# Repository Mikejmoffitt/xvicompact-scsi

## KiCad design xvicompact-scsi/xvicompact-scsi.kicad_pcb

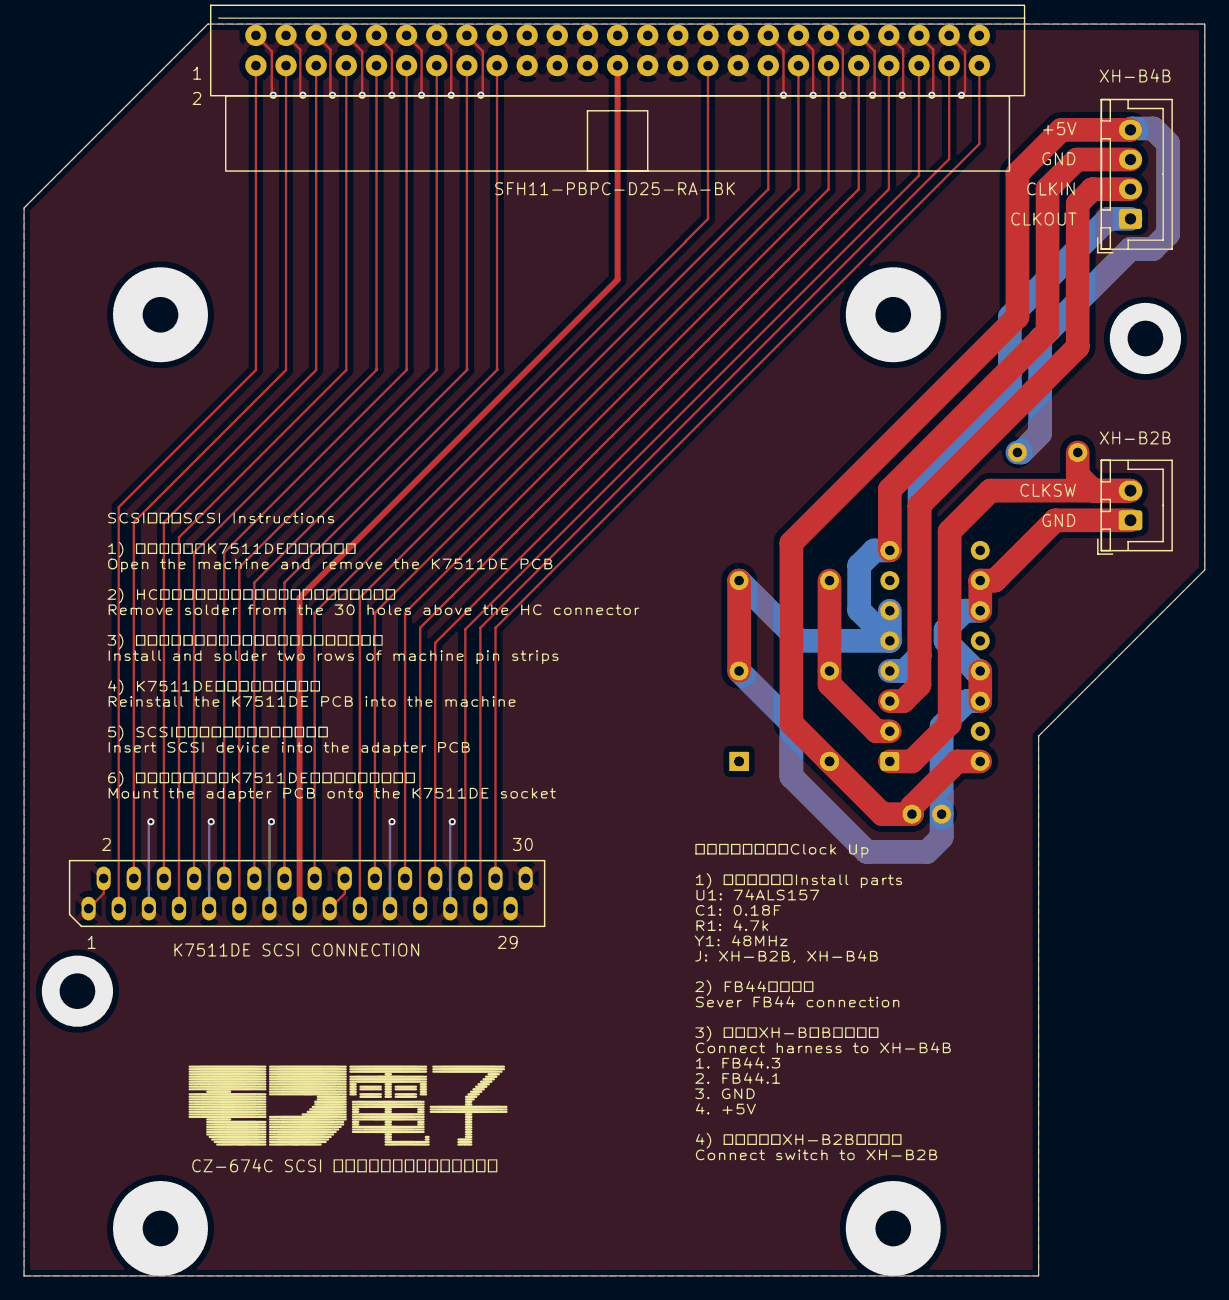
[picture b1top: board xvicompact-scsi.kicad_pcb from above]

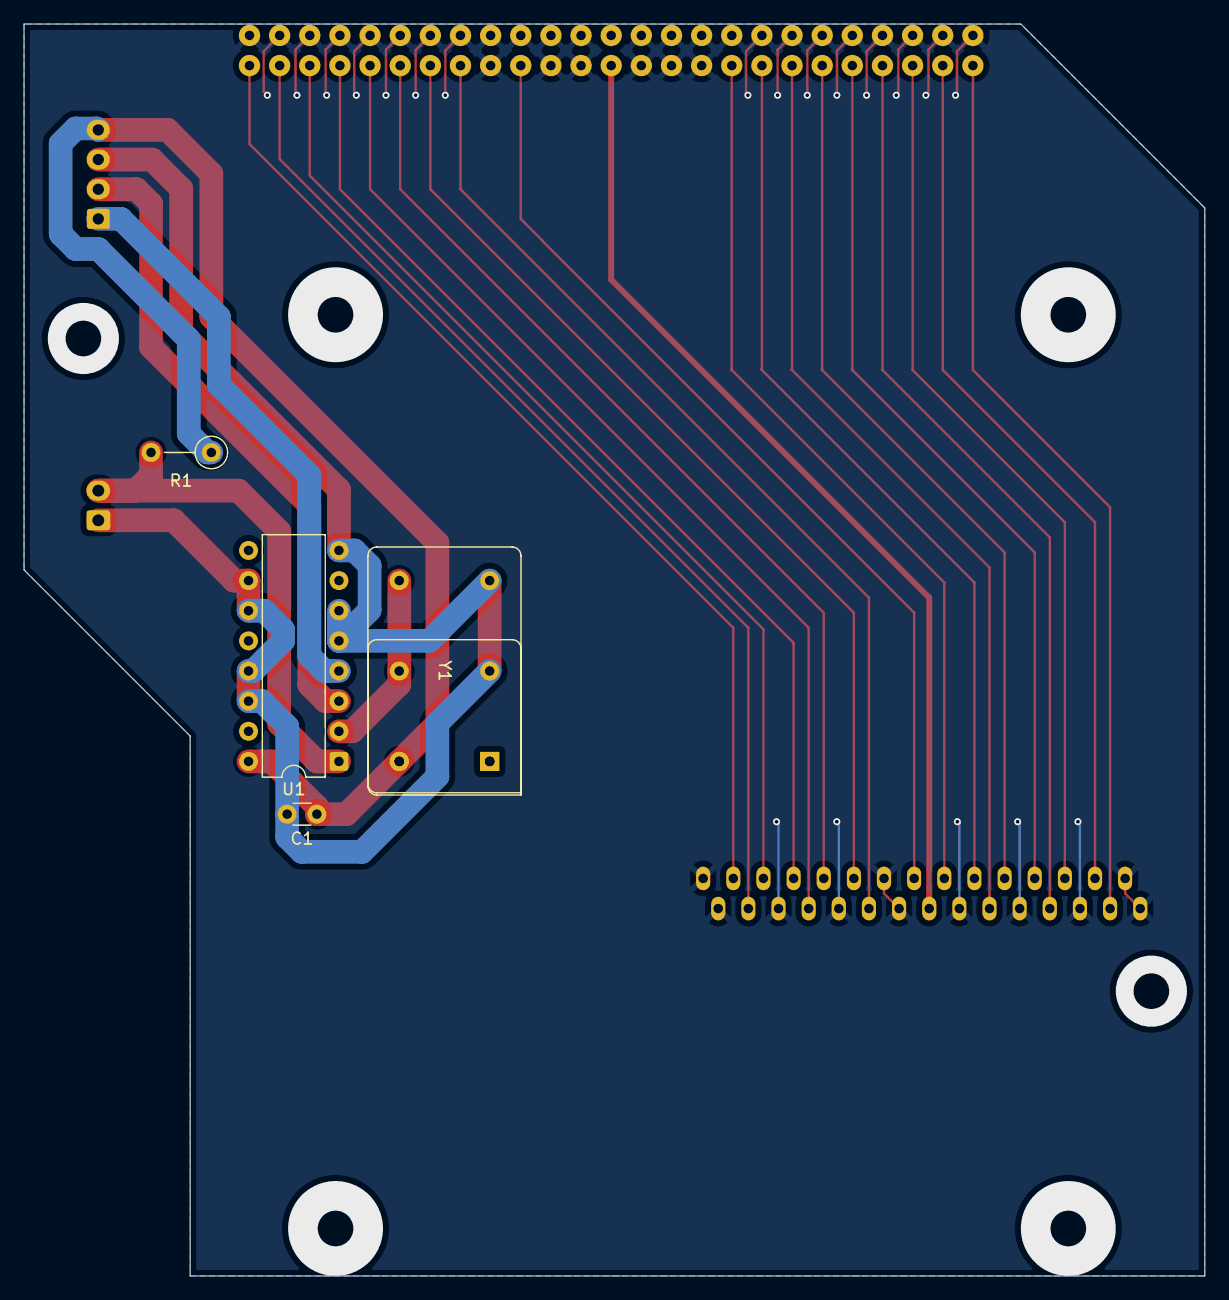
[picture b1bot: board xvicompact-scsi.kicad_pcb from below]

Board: 2 copper layers, 99.5 x 105.5 mm, 9 parts (5 on the bottom side), 26 nets.

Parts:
C1: 104; C_Disc_D3.0mm_W1.6mm_P2.50mm
J1: Conn_01x30; ZIP-30
J2: SFH11-PBPC-D25-RA-BK; SCSI-SOCKET-RA
J3: JST_XH_B2B-XH-A; JST_XH_B2B-XH-A_1x02_P2.50mm_Vertical
J4: JST_XH_B4B-XH-A; JST_XH_B4B-XH-A_1x04_P2.50mm_Vertical
R1: 4.7k; R_Axial_DIN0207_L6.3mm_D2.5mm_P5.08mm_Vertical
U1: 74ALS157; DIP-16_W7.62mm
Y1: CXO_DIP14; Oscillator_DIP-14
Y2: CXO_DIP8; Oscillator_DIP-8

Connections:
/CLKHI: U1.2 (I0a), Y1.8 (OUT), Y2.5 (OUT)
/CLKIN: J4.2, U1.3 (I1a)
/CLKOUT: J4.1, U1.4 (Za)
/CLKSW: J3.2, R1.2, U1.1 (S)
/DB0: J1.3, J2.2
/DB1: J1.4, J2.4
/DB2: J1.6, J2.6
/DB3: J1.7, J2.8
/DB4: J1.8, J2.10
/DB5: J1.10, J2.12
/DB6: J1.11, J2.14
/DB7: J1.12, J2.16
/PARITY: J1.14, J2.18
/TMPWR: J1.15, J2.26
/~ACK: J1.20, J2.38
/~ATN: J1.16, J2.32
/~BSY: J1.19, J2.36
/~C/D: J1.26, J2.46
/~I/O: J1.28, J2.50
/~MSG: J1.23, J2.42
/~REQ: J1.27, J2.48
/~RST: J1.22, J2.40
/~SEL: J1.24, J2.44
GND: C1.2, J3.1, J4.3, U1.5 (I0b), U1.6 (I1b), U1.8 (GND), U1.10 (I1c), U1.11 (I0c), U1.13 (I1d), U1.14 (I0d), Y1.7 (GND), Y2.4 (GND)
SGND: J1.1, J1.2, J1.5, J1.9, J1.13, J1.17, J1.18, J1.21, J1.25, J1.29, J1.30, J2.1, J2.3, J2.5, J2.7, J2.9, J2.11, J2.13, J2.15, J2.17, J2.19, J2.20, J2.21, J2.22, J2.23, J2.24, J2.27, J2.28, J2.29, J2.30, J2.31, J2.33, J2.34, J2.35, J2.37, J2.39, J2.41, J2.43, J2.45, J2.47, J2.49
VCC: C1.1, J4.4, R1.1, U1.16 (VCC), Y1.14 (Vcc), Y2.8 (Vcc)

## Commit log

2025-06-07 I think at this point I should just right angle it
